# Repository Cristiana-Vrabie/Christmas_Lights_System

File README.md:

# Christmas_Lights_System
## Introducere

Proiectul consta in realizarea unui sistem inteligent de iluminare RGB controlabil de la distanta utilizand tehnologia Bluetooth.
Sistemul va fi implementat utilizand microcontroller-ul PIC18F24Q10 de la Microchip. 
## Descrierea sistemului
Proiectul presupune comandarea unei benzi led RGB de la distanta prin intermediul unui modul Bluetooth HC-05, conexiunea cu microcontroller-ul fiind realizata prin comunicatia seriala (UART).
### Parti componente
#### Microcontroller PIC18F24Q10;
 PIC18 Core with 83 Instructions, 31 Stack Levels
 - Internal 64MHz oscillator
 - Operating Voltage Range:- 1.8V – 5.5V
 - 32 KB Flash Program Memory with self read/write capability
 - 2048 Bytes Data SRAM Memory
 - 256 Bytes of EEPROM
 - 10-bit ADC with computation, 24 channels
 - 1 x 5-bit DAC
 - 2 x Comparators
 - Fixed Voltage Reference (FVR) module - 1.024V, 2.048V and 4.096V output levels
 - Hardware Capacitive Voltage Divider (CVD) for mTouch buttons/sliders
 - 1 x Zero-Cross Detect
 - 1 x I2C/SPI
 - 1 x EUSART with LIN support
 - CRC with Memory Scan
 - Windowed Watchdog Timer (WWDT)
 - 1 x Hardware Limit Timer (HLT)
 - 1 x Complementary Waveform Generator
 - 2 x standalone 10-bit PWM modules
 - 2 x Capture/Compare/PWM modules
 - Three 8-bit Timers/Counters
 - Four 16-bit Timers/Counters
 - 1 x Hardware Limit Timer (HLT)
 - Extended Watchdog Timer (WDT)
 - Doze, Idle, and Sleep Power Saving Operating Modes
 - Low Current Power-on Reset (POR)
 - Brown-out Reset (BOR)
 - Low-Power BOR (LPBOR)
 - Peripheral Pin Select
 - In-Circuit Debug Integrated On-Chip
 - In-Circuit Serial Programing (ICSP) via Two Pins

#### Modul Bluetooth HC-05 (UART); (TBD)
 - Tensiune alimentare: 3.6V - 6V
 - Consum: 30mA
 - Rază acoperire: max. 100m
 - Folosește protocolul IEEE 802.15.1 standardizat
 - Poate fi opera atât ca Master cât și Slave
 - Baud Rate: 9600, 19200, 38400, 57600, 115200, 230400, 460800
 
#### Banda led RGB 12V (14W/m);
 - Tip Banda LED
 - Schimbare culoare lumina Da
 - Culoare lumina RGB/Multicolor
 - Intensitate luminoasa (LM)720 lm/ml
 - Lungime (cm)500
 - Grad de protectie (IP)IP54
 - Material Silicon
 - Clasa energetica A+
 
#### Tranzistor TIP41C (PWM);
 - Transistor Polarity: NPN
 - Collector Emitter Voltage V(br)ceo: 100V
 - DC Collector Current: 6A
 - Power Dissipation Pd: 65W
 - Transistor Case Style: TO-220
 - Transistor Mounting: Through Hole
 - No. of Pins: 3Pins
 - Transition Frequency ft: -
 - DC Current Gain hFE: 15hFE
 - Operating Temperature Max: 150°C
 - Product Range: -
 - Automotive Qualification Standard: -
 
#### Senzor de lumina ambientala TEMT6000 (ADC). (TBD)
 - Collector-emitter voltage: 6 V
 - Collector-emitter voltage: 1.5 V
 - Maximum Current: 20 mA
 - Power supply mode: 3.3 V to 5 V
 - Wavelength: 570 nm
 - Detection angle: 60 °
 - Dimensions: 14 x 8 mm

#### Sursa de alimentare
 - 24W, 12V, 2A
 
#### PICkit3
 - Full-speed USB support using Windows standard drivers
 - Real-time execution
 - Processors run at maximum speeds
 - Built-in over-voltage/short circuit monitor
 - Low voltage to 5V (1.8-5V range)
 - Diagnostic LEDs (power, active, status)
 - Read/write program and data memory of microcontroller
 - Erase of all memory types (EEPROM, ID, configuration and program) with verification
 - Peripheral freeze at breakpoint

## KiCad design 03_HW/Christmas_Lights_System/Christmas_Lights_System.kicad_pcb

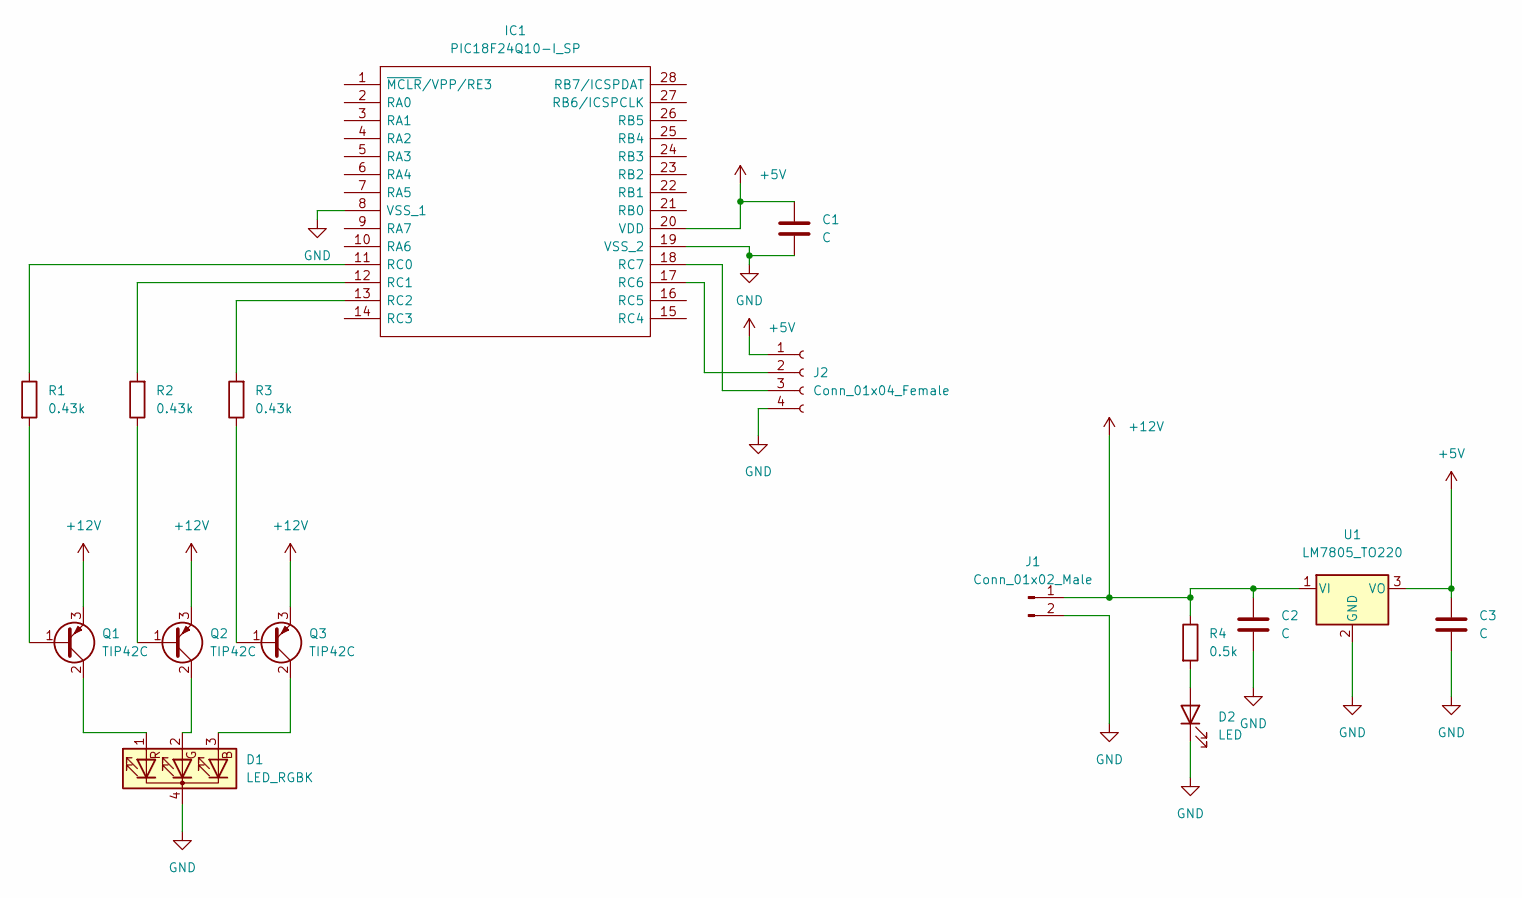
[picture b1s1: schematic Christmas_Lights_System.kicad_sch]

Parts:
C1, C2, C3: C; C_Axial_L3.8mm_D2.6mm_P7.50mm_Horizontal
D1: LED_RGBK; PinHeader_1x04_P2.54mm_Vertical
D2: LED; PinHeader_1x02_P2.54mm_Vertical
IC1: PIC18F24Q10-I_SP; DIP794W56P254L3486H508Q28N; Manufacturer_Part_Number PIC18F24Q10-I/SP; Mouser Part Number 579-PIC18F24Q10-I/SP
J1: Conn_01x02_Male; JWT_A3963_1x02_P3.96mm_Vertical
J2: Conn_01x04_Female; FanPinHeader_1x04_P2.54mm_Vertical
Q1, Q2, Q3: TIP42C; TO-220-3_Vertical
R1, R2, R3: 0.43k; R_Axial_DIN0411_L9.9mm_D3.6mm_P7.62mm_Vertical
R4: 0.5k; R_Axial_DIN0411_L9.9mm_D3.6mm_P7.62mm_Vertical
U1: LM7805_TO220; TO-220-3_Vertical

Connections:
+5V: C1.1, C3.1, IC1.20 (VDD), J2.1 (VCC), U1.3 (VO)
+12V: C2.1, J1.1, Q1.3 (E), Q2.3 (E), Q3.3 (E), R4.1, U1.1 (VI)
GND: C1.2, C2.2, C3.2, D1.4 (K), D2.1 (K), IC1.8 (VSS_1), IC1.19 (VSS_2), J1.2, J2.4 (VSS), U1.2 (GND)
unnamed: D1.1 (RA), Q1.2 (C)
unnamed: D1.2 (GA), Q2.2 (C)
unnamed: D1.3 (BA), Q3.2 (C)
unnamed: D2.2 (A), R4.2
unnamed: IC1.11 (RC0), R1.1
unnamed: IC1.12 (RC1), R2.2
unnamed: IC1.13 (RC2), R3.2
unnamed: IC1.17 (RC6), J2.2 (RX)
unnamed: IC1.18 (RC7), J2.3 (TX)
unnamed: Q1.1 (B), R1.2
unnamed: Q2.1 (B), R2.1
unnamed: Q3.1 (B), R3.1

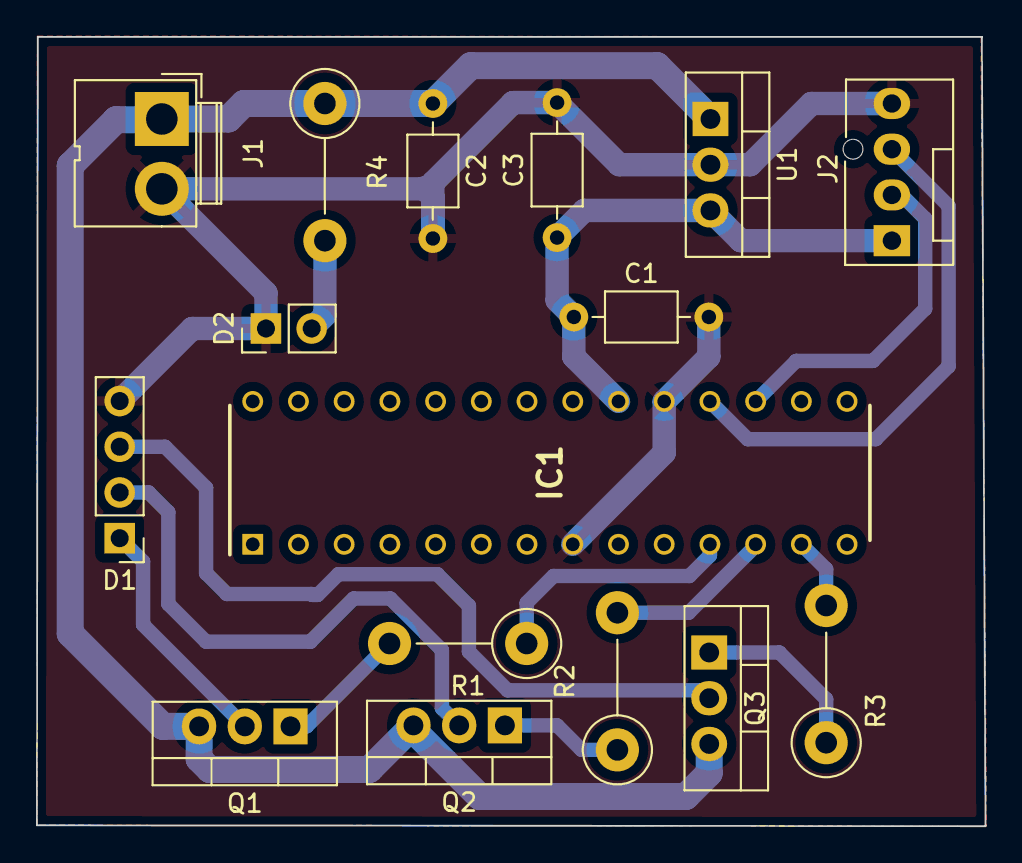
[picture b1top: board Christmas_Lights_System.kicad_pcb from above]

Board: 2 copper layers, 52.7 x 43.9 mm, 16 parts (0 on the bottom side), 15 nets.

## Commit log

2021-10-25 -added readme.md
2021-11-16 first version of code
2021-11-16 added DIO&TYPES
2021-11-16 added set_pin_level and set_pin_direction functions
2021-12-16 -added function for reading the pin voltage
2022-01-03 -first version of schematic
2022-01-04 -updated schematic -initial version of PCB layout
2022-01-04 -added pcb results product
2022-01-16 -added pwm and timer
2022-01-16 -release 1.0
